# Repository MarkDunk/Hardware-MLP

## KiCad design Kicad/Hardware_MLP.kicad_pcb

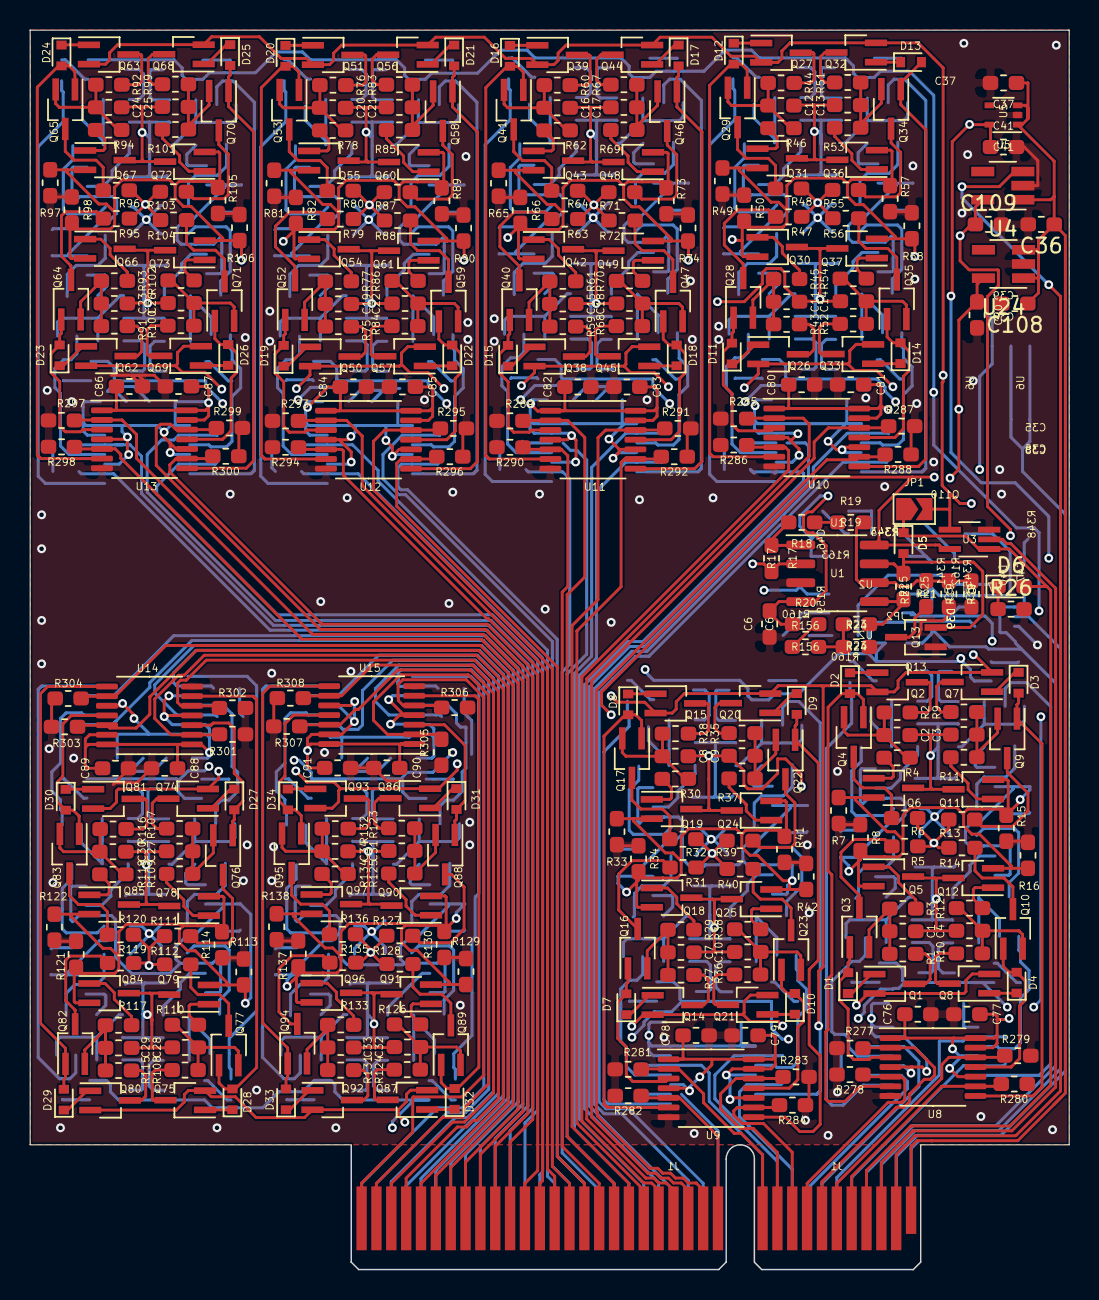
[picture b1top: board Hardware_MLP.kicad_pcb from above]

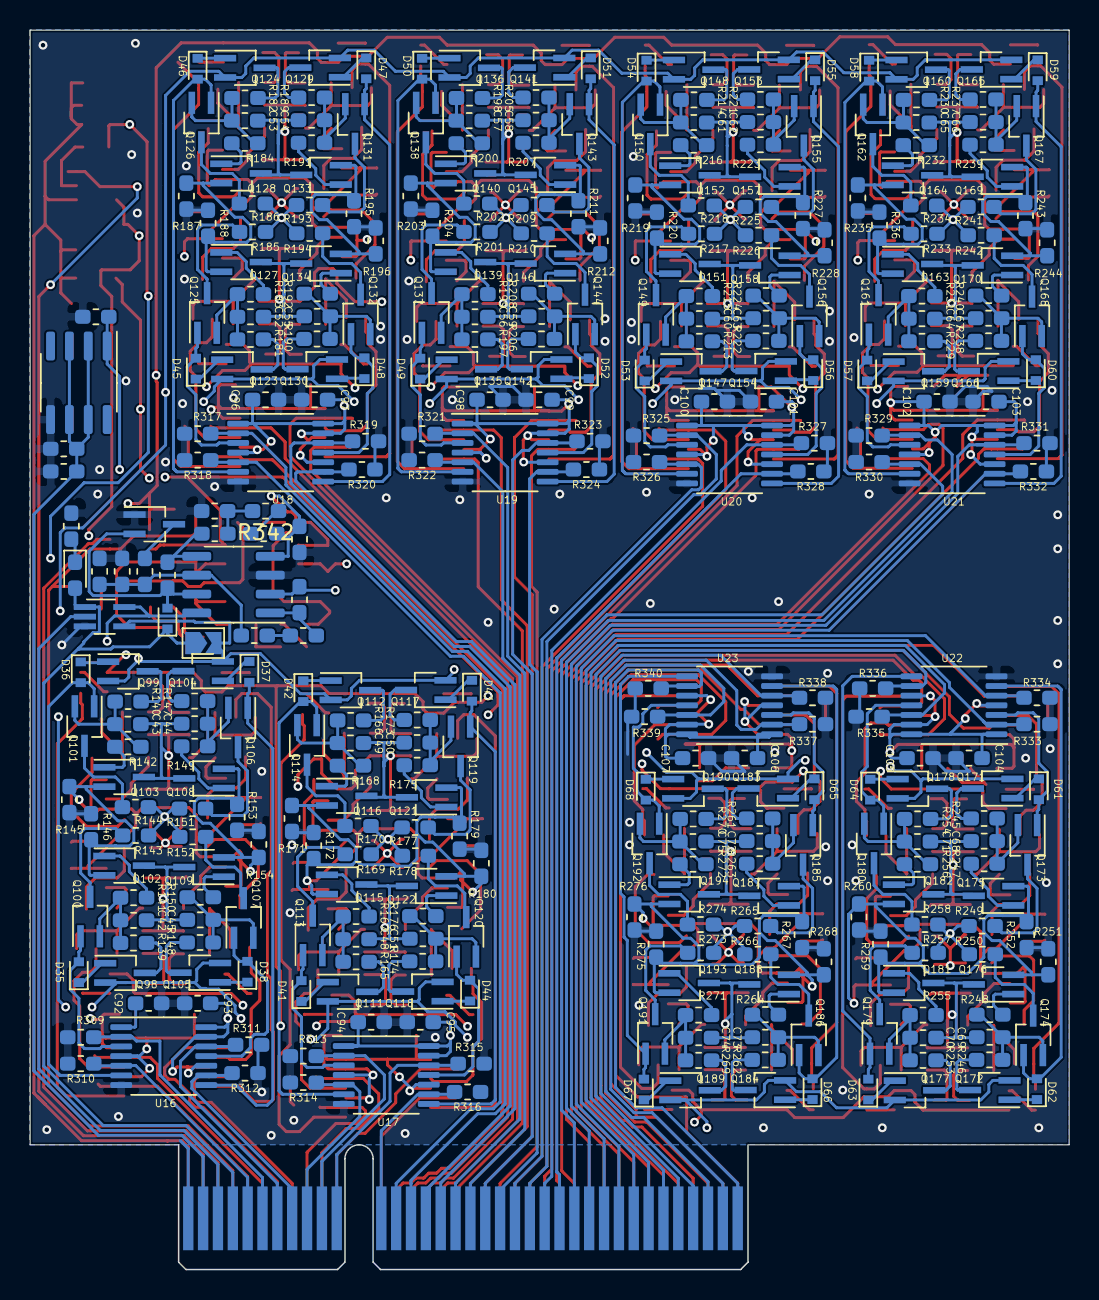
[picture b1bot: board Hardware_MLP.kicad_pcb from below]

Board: 4 copper layers, 70.0 x 83.5 mm, 740 parts (368 on the bottom side), 482 nets.

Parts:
C1, C2, C3, C4, C7, C8, C9, C10, C11, C12, C13, C14, C15, C16, C17, C18, C19, C20, C21, C22, C23, C24, C25, C26, C27, C28, C29, C30, C31, C32, C33, C34, C42, C43, C44, C45, C48, C49, C50, C51, C52, C53, C54, C55, C56, C57, C58, C59, C60, C61, C62, C63, C64, C65, C66, C67, C68, C69, C70, C71, C72, C73, C74, C75: 10uF; C_0603_1608Metric_Pad1.05x0.95mm_HandSolder
C5, C47: 4.7uF; C_0603_1608Metric_Pad1.05x0.95mm_HandSolder
C6, C36, C39, C46, C76, C78, C80, C82, C84, C86, C88, C90, C92, C94, C96, C98, C100, C102, C104, C106, C108: .1uF; C_0603_1608Metric_Pad1.05x0.95mm_HandSolder
C35, C37, C40, C41, C77, C79, C81, C83, C85, C87, C89, C91, C93, C95, C97, C99, C101, C103, C105, C107, C109: 1uF; C_0603_1608Metric_Pad1.05x0.95mm_HandSolder
C38: .33uF; C_0603_1608Metric_Pad1.05x0.95mm_HandSolder
D1, D2, D3, D4, D5, D7, D8, D9, D10, D11, D12, D13, D14, D15, D16, D17, D18, D19, D20, D21, D22, D23, D24, D25, D26, D27, D28, D29, D30, D31, D32, D33, D34, D35, D36, D37, D38, D39, D41, D42, D43, D44, D45, D46, D47, D48, D49, D50, D51, D52, D53, D54, D55, D56, D57, D58, D59, D60, D61, D62, D63, D64, D65, D66, D67, D68: RB521S-30; D_SOD-523
D6, D40: LED; LED_0603_1608Metric_Pad1.05x0.95mm_HandSolder
J1: Neuron_Board_Edge; BUS_PCIexpress_x8
JP1, JP2: SolderJumper_2_Open; SolderJumper-2_P1.3mm_Open_TrianglePad1.0x1.5mm
Q1, Q2, Q3, Q4, Q5, Q6, Q7, Q8, Q9, Q10, Q11, Q12, Q13, Q14, Q15, Q16, Q17, Q18, Q19, Q20, Q21, Q22, Q23, Q24, Q25, Q26, Q27, Q28, Q29, Q30, Q31, Q32, Q33, Q34, Q35, Q36, Q37, Q38, Q39, Q40, Q41, Q42, Q43, Q44, Q45, Q46, Q47, Q48, Q49, Q50, Q51, Q52, Q53, Q54, Q55, Q56, Q57, Q58, Q59, Q60, Q61, Q62, Q63, Q64, Q65, Q66, Q67, Q68, Q69, Q70, Q71, Q72, Q73, Q74, Q75, Q76, Q77, Q78, Q79, Q80, Q81, Q82, Q83, Q84, Q85, Q86, Q87, Q88, Q89, Q90, Q91, Q92, Q93, Q94, Q95, Q96, Q97, Q98, Q99, Q100, Q101, Q102, Q103, Q104, Q105, Q106, Q107, Q108, Q109, Q110, Q111, Q112, Q113, Q114, Q115, Q116, Q117, Q118, Q119, Q120, Q121, Q122, Q123, Q124, Q125, Q126, Q127, Q128, Q129, Q130, Q131, Q132, Q133, Q134, Q135, Q136, Q137, Q138, Q139, Q140, Q141, Q142, Q143, Q144, Q145, Q146, Q147, Q148, Q149, Q150, Q151, Q152, Q153, Q154, Q155, Q156, Q157, Q158, Q159, Q160, Q161, Q162, Q163, Q164, Q165, Q166, Q167, Q168, Q169, Q170, Q171, Q172, Q173, Q174, Q175, Q176, Q177, Q178, Q179, Q180, Q181, Q182, Q183, Q184, Q185, Q186, Q187, Q188, Q189, Q190, Q191, Q192, Q193, Q194: 2SK3018; SOT-323_SC-70_Handsoldering
R1, R2, R3, R4, R7, R8, R9, R10, R11, R12, R15, R16, R27, R28, R29, R30, R33, R34, R35, R36, R37, R38, R41, R42, R43, R44, R45, R46, R49, R50, R51, R52, R53, R54, R57, R58, R59, R60, R61, R62, R65, R66, R67, R68, R69, R70, R73, R74, R75, R76, R77, R78, R81, R82, R83, R84, R85, R86, R89, R90, R91, R92, R93, R94, R97, R98, R99, R100, R101, R102, R105, R106, R107, R108, R109, R110, R113, R114, R115, R116, R117, R118, R121, R122, R123, R124, R125, R126, R129, R130, R131, R132, R133, R134, R137, R138, R139, R140, R141, R142, R145, R146, R147, R148, R149, R150, R153, R154, R165, R166, R167, R168, R171, R172, R173, R174, R175, R176, R179, R180, R181, R182, R183, R184, R187, R188, R189, R190, R191, R192, R195, R196, R197, R198, R199, R200, R203, R204, R205, R206, R207, R208, R211, R212, R213, R214, R215, R216, R219, R220, R221, R222, R223, R224, R227, R228, R229, R230, R231, R232, R235, R236, R237, R238, R239, R240, R243, R244, R245, R246, R247, R248, R251, R252, R253, R254, R255, R256, R259, R260, R261, R262, R263, R264, R267, R268, R269, R270, R271, R272, R275, R276: 100K; R_0603_1608Metric_Pad1.05x0.95mm_HandSolder
R5, R6, R13, R14, R31, R32, R39, R40, R47, R48, R55, R56, R63, R64, R71, R72, R79, R80, R87, R88, R95, R96, R103, R104, R111, R112, R119, R120, R127, R128, R135, R136, R143, R144, R151, R152, R169, R170, R177, R178, R185, R186, R193, R194, R201, R202, R209, R210, R217, R218, R225, R226, R233, R234, R241, R242, R249, R250, R257, R258, R265, R266, R273, R274: 1.5K; R_0603_1608Metric_Pad1.05x0.95mm_HandSolder
R17, R21, R159, R341: 100; R_0603_1608Metric_Pad1.05x0.95mm_HandSolder
R18, R160, R160#2: Rc; R_0603_1608Metric_Pad1.05x0.95mm_HandSolder
R19, R19#2, R23, R24, R25, R156, R162, R343, R344, R345: 10K; R_0603_1608Metric_Pad1.05x0.95mm_HandSolder
R20, R163: 20K; R_0603_1608Metric_Pad1.05x0.95mm_HandSolder
R26, R348: R_LED; R_0603_1608Metric_Pad1.05x0.95mm_HandSolder
R277, R278, R279, R280, R281, R282, R283, R284, R285, R286, R287, R288, R289, R290, R291, R292, R293, R294, R295, R296, R297, R298, R299, R300, R301, R302, R303, R304, R305, R306, R307, R308, R309, R310, R311, R312, R313, R314, R315, R316, R317, R318, R319, R320, R321, R322, R323, R324, R325, R326, R327, R328, R329, R330, R331, R332, R333, R334, R335, R336, R337, R338, R339, R340: 10k; R_0603_1608Metric_Pad1.05x0.95mm_HandSolder
R342: R_0603_1608Metric_Pad1.05x0.95mm_HandSolder
U1, U2: AZ4580; SOIC-8_3.9x4.9mm_P1.27mm
U3, U7: 74AHC1G08; SOT-353_SC-70-5_Handsoldering
U4, U24: TCR2EF; SOT-23-5_HandSoldering
U5: MIC5365-1.2YC5; SOT-353_SC-70-5
U6: MC79L05_SO8; SOIC-8_3.9x4.9mm_P1.27mm
U8, U9, U10, U11, U12, U13, U14, U15, U16, U17, U18, U19, U20, U21, U22, U23: SN74AHCT126; TSSOP-14_4.4x5mm_P0.65mm

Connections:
/5V5: C36.1, C37.1, C108.1, J1.A1, U4.1, U5.1, U5.3, U24.1, U24.3
/-10V: C35.2, C38.2, J1.B2, U6.2, U6.3, U6.6, U6.7
/A Side/Hebb: JP1.2, Q1.2, Q2.2, Q7.2, Q8.2, Q14.2, Q15.2, Q20.2, Q21.2, Q26.2, Q27.2, Q32.2, Q33.2, Q38.2, Q39.2, Q44.2, Q45.2, Q50.2, Q51.2, Q56.2, Q57.2, Q62.2, Q63.2, Q68.2, Q69.2, Q74.2, Q75.2, Q80.2, Q81.2, Q86.2, Q87.2, Q92.2, Q93.2, U3.4
/A Side/WX: R5.1, R6.1, R13.1, R14.1, R17.2, R31.1, R32.1, R39.1, R40.1, R47.1, R48.1, R55.1, R56.1, R63.1, R64.1, R71.1, R72.1, R79.1, R80.1, R87.1, R88.1, R95.1, R96.1, R103.1, R104.1, R111.1, R112.1, R119.1, R120.1, R127.1, R128.1, R135.1, R136.1, U1.2
/A Side/Weight Section 1/X1_CL: D1.2, Q3.1, U8.3
/A Side/Weight Section 1/X2_CL: D2.2, Q4.1, U8.6
/A Side/Weight Section 1/X3_CL: D3.2, Q9.1, U8.8
/A Side/Weight Section 1/X4_CL: D4.2, Q10.1, U8.11
/A Side/sheet60210D35/X1_CL: D19.2, Q52.1, U12.3
/A Side/sheet60210D35/X2_CL: D20.2, Q53.1, U12.6
/A Side/sheet60210D35/X3_CL: D21.2, Q58.1, U12.8
/A Side/sheet60210D35/X4_CL: D22.2, Q59.1, U12.11
/A Side/sheet60210D36/X1_CL: D23.2, Q64.1, U13.3
/A Side/sheet60210D36/X2_CL: D24.2, Q65.1, U13.6
/A Side/sheet60210D36/X3_CL: D25.2, Q70.1, U13.8
/A Side/sheet60210D36/X4_CL: D26.2, Q71.1, U13.11
/A Side/sheet60210D37/X1_CL: D27.2, Q76.1, U14.3
/A Side/sheet60210D37/X2_CL: D28.2, Q77.1, U14.6
/A Side/sheet60210D37/X3_CL: D29.2, Q82.1, U14.8
/A Side/sheet60210D37/X4_CL: D30.2, Q83.1, U14.11
/A Side/sheet60210D38/X1_CL: D31.2, Q88.1, U15.3
/A Side/sheet60210D38/X2_CL: D32.2, Q89.1, U15.6
/A Side/sheet60210D38/X3_CL: D33.2, Q94.1, U15.8
/A Side/sheet60210D38/X4_CL: D34.2, Q95.1, U15.11
/A Side/sheet602109E3/X1_CL: D11.2, Q28.1, U10.3
/A Side/sheet602109E3/X2_CL: D12.2, Q29.1, U10.6
/A Side/sheet602109E3/X3_CL: D13.2, Q34.1, U10.8
/A Side/sheet602109E3/X4_CL: D14.2, Q35.1, U10.11
/A Side/sheet602109E4/X1_CL: D15.2, Q40.1, U11.3
/A Side/sheet602109E4/X2_CL: D16.2, Q41.1, U11.6
/A Side/sheet602109E4/X3_CL: D17.2, Q46.1, U11.8
/A Side/sheet602109E4/X4_CL: D18.2, Q47.1, U11.11
/A Side/sheet6021083A/X1_CL: D7.2, Q16.1, U9.3
/A Side/sheet6021083A/X2_CL: D8.2, Q17.1, U9.6
/A Side/sheet6021083A/X3_CL: D9.2, Q22.1, U9.8
/A Side/sheet6021083A/X4_CL: D10.2, Q23.1, U9.11
/B Side/Hebb: JP2.2, Q98.2, Q99.2, Q104.2, Q105.2, Q111.2, Q112.2, Q117.2, Q118.2, Q123.2, Q124.2, Q129.2, Q130.2, Q135.2, Q136.2, Q141.2, Q142.2, Q147.2, Q148.2, Q153.2, Q154.2, Q159.2, Q160.2, Q165.2, Q166.2, Q171.2, Q172.2, Q177.2, Q178.2, Q183.2, Q184.2, Q189.2, Q190.2, U7.4
/B Side/WX: R143.1, R144.1, R151.1, R152.1, R159.2, R169.1, R170.1, R177.1, R178.1, R185.1, R186.1, R193.1, R194.1, R201.1, R202.1, R209.1, R210.1, R217.1, R218.1, R225.1, R226.1, R233.1, R234.1, R241.1, R242.1, R249.1, R250.1, R257.1, R258.1, R265.1, R266.1, R273.1, R274.1, U2.2
/B Side/Weight Section 1/X1_CL: D35.2, Q100.1, U16.3
/B Side/Weight Section 1/X2_CL: D36.2, Q101.1, U16.6
/B Side/Weight Section 1/X3_CL: D37.2, Q106.1, U16.8
/B Side/Weight Section 1/X4_CL: D38.2, Q107.1, U16.11
/B Side/sheet60210D35/X1_CL: D53.2, Q149.1, U20.3
/B Side/sheet60210D35/X2_CL: D54.2, Q150.1, U20.6
/B Side/sheet60210D35/X3_CL: D55.2, Q155.1, U20.8
/B Side/sheet60210D35/X4_CL: D56.2, Q156.1, U20.11
/B Side/sheet60210D36/X1_CL: D57.2, Q161.1, U21.3
/B Side/sheet60210D36/X2_CL: D58.2, Q162.1, U21.6
/B Side/sheet60210D36/X3_CL: D59.2, Q167.1, U21.8
/B Side/sheet60210D36/X4_CL: D60.2, Q168.1, U21.11
/B Side/sheet60210D37/X1_CL: D61.2, Q173.1, U22.3
/B Side/sheet60210D37/X2_CL: D62.2, Q174.1, U22.6
/B Side/sheet60210D37/X3_CL: D63.2, Q179.1, U22.8
/B Side/sheet60210D37/X4_CL: D64.2, Q180.1, U22.11
/B Side/sheet60210D38/X1_CL: D65.2, Q185.1, U23.3
/B Side/sheet60210D38/X2_CL: D66.2, Q186.1, U23.6
/B Side/sheet60210D38/X3_CL: D67.2, Q191.1, U23.8
/B Side/sheet60210D38/X4_CL: D68.2, Q192.1, U23.11
/B Side/sheet602109E3/X1_CL: D45.2, Q125.1, U18.3
/B Side/sheet602109E3/X2_CL: D46.2, Q126.1, U18.6
/B Side/sheet602109E3/X3_CL: D47.2, Q131.1, U18.8
/B Side/sheet602109E3/X4_CL: D48.2, Q132.1, U18.11
/B Side/sheet602109E4/X1_CL: D49.2, Q137.1, U19.3
/B Side/sheet602109E4/X2_CL: D50.2, Q138.1, U19.6
/B Side/sheet602109E4/X3_CL: D51.2, Q143.1, U19.8
/B Side/sheet602109E4/X4_CL: D52.2, Q144.1, U19.11
/B Side/sheet6021083A/X1_CL: D41.2, Q113.1, U17.3
/B Side/sheet6021083A/X2_CL: D42.2, Q114.1, U17.6
/B Side/sheet6021083A/X3_CL: D43.2, Q119.1, U17.8
/B Side/sheet6021083A/X4_CL: D44.2, Q120.1, U17.11
/F(X)A: D5.1, D6.2, J1.A4, JP1.1, U3.1
/F(X)B: D39.1, D40.2, J1.B4, JP2.1, U7.1
/Train: J1.A2, U4.3
/Vgsbias: C1.2, C2.2, C3.2, C4.2, C7.2, C8.2, C9.2, C10.2, C11.2, C12.2, C13.2, C14.2, C15.2, C16.2, C17.2, C18.2, C19.2, C20.2, C21.2, C22.2, C23.2, C24.2, C25.2, C26.2, C27.2, C28.2, C29.2, C30.2, C31.2, C32.2, C33.2, C34.2, C41.1, C42.2, C43.2, C44.2, C45.2, C48.2, C49.2, C50.2, C51.2, C52.2, C53.2, C54.2, C55.2, C56.2, C57.2, C58.2, C59.2, C60.2, C61.2, C62.2, C63.2, C64.2, C65.2, C66.2, C67.2, C68.2, C69.2, C70.2, C71.2, C72.2, C73.2, C74.2, C75.2, Q5.3, Q6.3, Q11.3, Q12.3, Q18.3, Q19.3, Q24.3, Q25.3, Q30.3, Q31.3, Q36.3, Q37.3, Q42.3, Q43.3, Q48.3, Q49.3, Q54.3, Q55.3, Q60.3, Q61.3, Q66.3, Q67.3, Q72.3, Q73.3, Q78.3, Q79.3, Q84.3, Q85.3, Q90.3, Q91.3, Q96.3, Q97.3, Q102.3, Q103.3, Q108.3, Q109.3, Q115.3, Q116.3, Q121.3, Q122.3, Q127.3, Q128.3, Q133.3, Q134.3, Q139.3, Q140.3, Q145.3, Q146.3, Q151.3, Q152.3, Q157.3, Q158.3, Q163.3, Q164.3, Q169.3, Q170.3, Q175.3, Q176.3, Q181.3, Q182.3, Q187.3, Q188.3, Q193.3, Q194.3, U5.5
/Vs-: C6.2, C39.2, C46.2, R20.1, R163.1, U1.4, U2.4, U6.1
/Vtrain: C109.1, Q5.2, Q6.2, Q11.2, Q12.2, Q18.2, Q19.2, Q24.2, Q25.2, Q30.2, Q31.2, Q36.2, Q37.2, Q42.2, Q43.2, Q48.2, Q49.2, Q54.2, Q55.2, Q60.2, Q61.2, Q66.2, Q67.2, Q72.2, Q73.2, Q78.2, Q79.2, Q84.2, Q85.2, Q90.2, Q91.2, Q96.2, Q97.2, Q102.2, Q103.2, Q108.2, Q109.2, Q115.2, Q116.2, Q121.2, Q122.2, Q127.2, Q128.2, Q133.2, Q134.2, Q139.2, Q140.2, Q145.2, Q146.2, Q151.2, Q152.2, Q157.2, Q158.2, Q163.2, Q164.2, Q169.2, Q170.2, Q175.2, Q176.2, Q181.2, Q182.2, Q187.2, Q188.2, Q193.2, Q194.2, R7.1, R8.1, R15.1, R16.1, R33.1, R34.1, R41.1, R42.1, R49.1, R50.1, R57.1, R58.1, R65.1, R66.1, R73.1, R74.1, R81.1, R82.1, R89.1, R90.1, R97.1, R98.1, R105.1, R106.1, R113.1, R114.1, R121.1, R122.1, R129.1, R130.1, R137.1, R138.1, R145.1, R146.1, R153.1, R154.1, R171.1, R172.1, R179.1, R180.1, R187.1, R188.1, R195.1, R196.1, R203.1, R204.1, R211.1, R212.1, R219.1, R220.1, R227.1, R228.1, R235.1, R236.1, R243.1, R244.1, R251.1, R252.1, R259.1, R260.1, R267.1, R268.1, R275.1, R276.1, U4.5
/X1A: J1.A5, R278.1, U8.5
/X1B: J1.B5, R310.1, U16.5
/X2A: J1.A6, R277.1, U8.2
/X2B: J1.B6, R309.1, U16.2
/X3A: J1.A7, R279.2, U8.12
/X3B: J1.B7, R311.2, U16.12
/X4A: J1.A8, R280.2, U8.9
/X4B: J1.B8, R312.2, U16.9
/X5A: J1.A9, R284.2, U9.9
/X5B: J1.B9, R316.2, U17.9
/X6A: J1.A10, R283.2, U9.12
/X6B: J1.B10, R315.2, U17.12
/X7A: J1.A11, R281.1, U9.2
/X7B: J1.B11, R313.1, U17.2
/X8A: J1.A12, R282.1, U9.5
/X8B: J1.B12, R314.1, U17.5
/X9A: J1.A13, R288.2, U10.9
/X9B: J1.B13, R320.2, U18.9
/X10A: J1.A14, R287.2, U10.12
/X10B: J1.B14, R319.2, U18.12
/X11A: J1.A15, R285.1, U10.2
/X11B: J1.B15, R317.1, U18.2
/X12A: J1.A16, R286.1, U10.5
/X12B: J1.B16, R318.1, U18.5
/X13A: J1.A17, R292.2, U11.9
/X13B: J1.B17, R324.2, U19.9
/X14A: J1.A18, R291.2, U11.12
/X14B: J1.B18, R323.2, U19.12
/X15A: J1.A19, R289.1, U11.2
/X15B: J1.B19, R321.1, U19.2
/X16A: J1.A20, R290.1, U11.5
/X16B: J1.B20, R322.1, U19.5
/X17A: J1.A21, R296.2, U12.9
/X17B: J1.B21, R328.2, U20.9
/X18A: J1.A22, R295.2, U12.12
/X18B: J1.B22, R327.2, U20.12
/X19A: J1.A23, R293.1, U12.2
/X19B: J1.B23, R325.1, U20.2
/X20A: J1.A24, R294.1, U12.5
/X20B: J1.B24, R326.1, U20.5
/X21A: J1.A25, R300.2, U13.9
/X21B: J1.B25, R332.2, U21.9
/X22A: J1.A26, R299.2, U13.12
/X22B: J1.B26, R331.2, U21.12
/X23A: J1.A27, R297.1, U13.2
/X23B: J1.B27, R329.1, U21.2
/X24A: J1.A28, R298.1, U13.5
/X24B: J1.B28, R330.1, U21.5
/X25A: J1.A29, R304.2, U14.9
/X25B: J1.B29, R336.2, U22.9
/X26A: J1.A30, R303.2, U14.12
/X26B: J1.B30, R335.2, U22.12
/X27A: J1.A31, R301.1, U14.2
/X27B: J1.B31, R333.1, U22.2
/X28A: J1.A32, R302.1, U14.5
/X28B: J1.B32, R334.1, U22.5
/X29A: J1.A33, R308.2, U15.9
/X29B: J1.B33, R340.2, U23.9
/X30A: J1.A34, R307.2, U15.12
/X30B: J1.B34, R339.2, U23.12
/X31A: J1.A35, R305.1, U15.2
/X31B: J1.B35, R337.1, U23.2
/X32A: J1.A36, R306.1, U15.5
/X32B: J1.B36, R338.1, U23.5
/YA: J1.A3, U3.2
/YB: J1.B3, U7.2
GND: C5.2, C6.1, C35.1, C36.2, C37.2, C38.1, C39.1, C40.2, C41.2, C46.1, C47.2, C76.2, C77.2, C78.2, C79.2, C80.2, C81.2, C82.2, C83.2, C84.2, C85.2, C86.2, C87.2, C88.2, C89.2, C90.2, C91.2, C92.2, C93.2, C94.2, C95.2, C96.2, C97.2, C98.2, C99.2, C100.2, C101.2, C102.2, C103.2, C104.2, C105.2, C106.2, C107.2, C108.2, C109.2, J1.B1, Q13.1, Q110.1, R7.2, R8.2, R15.2, R16.2, R19#2.1, R24.2, R26.2, R33.2, R34.2, R41.2, R42.2, R49.2, R50.2, R57.2, R58.2, R65.2, R66.2, R73.2, R74.2, R81.2, R82.2, R89.2, R90.2, R97.2, R98.2, R105.2, R106.2, R113.2, R114.2, R121.2, R122.2, R129.2, R130.2, R137.2, R138.2, R145.2, R146.2, R153.2, R154.2, R162.1, R171.2, R172.2, R179.2, R180.2, R187.2, R188.2, R195.2, R196.2, R203.2, R204.2, R211.2, R212.2, R219.2, R220.2, R227.2, R228.2, R235.2, R236.2, R243.2, R244.2, R251.2, R252.2, R259.2, R260.2, R267.2, R268.2, R275.2, R276.2, R277.2, R278.2, R279.1, R280.1, R281.2, R282.2, R283.1, R284.1, R285.2, R286.2, R287.1, R288.1, R289.2, R290.2, R291.1, R292.1, R293.2, R294.2, R295.1, R296.1, R297.2, R298.2, R299.1, R300.1, R301.2, R302.2, R303.1, R304.1, R305.2, R306.2, R307.1, R308.1, R309.2, R310.2, R311.1, R312.1, R313.2, R314.2, R315.1, R316.1, R317.2, R318.2, R319.1, R320.1, R321.2, R322.2, R323.1, R324.1, R325.2, R326.2, R327.1, R328.1, R329.2, R330.2, R331.1, R332.1, R333.2, R334.2, R335.1, R336.1, R337.2, R338.2, R339.1, R340.1, R344.2, R348.2, U1.3, U2.3, U3.3, U4.2, U5.2, U6.5, U7.3, U8.7, U9.7, U10.7, U11.7, U12.7, U13.7, U14.7, U15.7, U16.7, U17.7, U18.7, U19.7, U20.7, U21.7, U22.7, U23.7, U24.2
unnamed: C1.1, Q3.2, R1.1, R3.2
unnamed: C2.1, Q4.2, R2.1, R4.2
unnamed: C3.1, Q9.2, R9.1, R11.2
unnamed: C4.1, Q10.2, R10.1, R12.2
unnamed: C5.1, R19.2, R19#2.2, R21.2, U1.6
unnamed: C7.1, Q16.2, R27.1, R29.2
unnamed: C8.1, Q17.2, R28.1, R30.2
unnamed: C9.1, Q22.2, R35.1, R37.2
unnamed: C10.1, Q23.2, R36.1, R38.2
unnamed: C11.1, Q28.2, R43.1, R45.2
unnamed: C12.1, Q29.2, R44.1, R46.2
unnamed: C13.1, Q34.2, R51.1, R53.2
unnamed: C14.1, Q35.2, R52.1, R54.2
unnamed: C15.1, Q40.2, R59.1, R61.2
unnamed: C16.1, Q41.2, R60.1, R62.2
unnamed: C17.1, Q46.2, R67.1, R69.2
unnamed: C18.1, Q47.2, R68.1, R70.2
unnamed: C19.1, Q52.2, R75.1, R77.2
unnamed: C20.1, Q53.2, R76.1, R78.2
unnamed: C21.1, Q58.2, R83.1, R85.2
unnamed: C22.1, Q59.2, R84.1, R86.2
unnamed: C23.1, Q64.2, R91.1, R93.2
unnamed: C24.1, Q65.2, R92.1, R94.2
unnamed: C25.1, Q70.2, R99.1, R101.2
unnamed: C26.1, Q71.2, R100.1, R102.2
unnamed: C27.1, Q76.2, R107.1, R109.2
unnamed: C28.1, Q77.2, R108.1, R110.2
unnamed: C29.1, Q82.2, R115.1, R117.2
unnamed: C30.1, Q83.2, R116.1, R118.2
unnamed: C31.1, Q88.2, R123.1, R125.2
unnamed: C32.1, Q89.2, R124.1, R126.2
unnamed: C33.1, Q94.2, R131.1, R133.2
unnamed: C34.1, Q95.2, R132.1, R134.2
unnamed: C42.1, Q100.2, R139.1, R141.2
unnamed: C43.1, Q101.2, R140.1, R142.2
unnamed: C44.1, Q106.2, R147.1, R149.2
unnamed: C45.1, Q107.2, R148.1, R150.2
unnamed: C47.1, R160.2, R162.2, R341.2, U2.6
unnamed: C48.1, Q113.2, R165.1, R167.2
unnamed: C49.1, Q114.2, R166.1, R168.2
unnamed: C50.1, Q119.2, R173.1, R175.2
unnamed: C51.1, Q120.2, R174.1, R176.2
unnamed: C52.1, Q125.2, R181.1, R183.2
unnamed: C53.1, Q126.2, R182.1, R184.2
unnamed: C54.1, Q131.2, R189.1, R191.2
unnamed: C55.1, Q132.2, R190.1, R192.2
unnamed: C56.1, Q137.2, R197.1, R199.2
unnamed: C57.1, Q138.2, R198.1, R200.2
unnamed: C58.1, Q143.2, R205.1, R207.2
unnamed: C59.1, Q144.2, R206.1, R208.2
unnamed: C60.1, Q149.2, R213.1, R215.2
unnamed: C61.1, Q150.2, R214.1, R216.2
unnamed: C62.1, Q155.2, R221.1, R223.2
unnamed: C63.1, Q156.2, R222.1, R224.2
unnamed: C64.1, Q161.2, R229.1, R231.2
unnamed: C65.1, Q162.2, R230.1, R232.2
unnamed: C66.1, Q167.2, R237.1, R239.2
unnamed: C67.1, Q168.2, R238.1, R240.2
unnamed: C68.1, Q173.2, R245.1, R247.2
unnamed: C69.1, Q174.2, R246.1, R248.2
unnamed: C70.1, Q179.2, R253.1, R255.2
unnamed: C71.1, Q180.2, R254.1, R256.2
unnamed: C72.1, Q185.2, R261.1, R263.2
unnamed: C73.1, Q186.2, R262.1, R264.2
unnamed: C74.1, Q191.2, R269.1, R271.2
unnamed: C75.1, Q192.2, R270.1, R272.2
unnamed: D1.1, Q1.1
unnamed: D2.1, Q2.1
unnamed: D3.1, Q7.1
unnamed: D4.1, Q8.1
unnamed: D5.2, Q13.2, U1.7
unnamed: D6.1, R26.1
unnamed: D7.1, Q14.1
unnamed: D8.1, Q15.1
unnamed: D9.1, Q20.1
unnamed: D10.1, Q21.1
unnamed: D11.1, Q26.1
unnamed: D12.1, Q27.1
unnamed: D13.1, Q32.1
unnamed: D14.1, Q33.1
unnamed: D15.1, Q38.1
unnamed: D16.1, Q39.1
unnamed: D17.1, Q44.1
unnamed: D18.1, Q45.1
unnamed: D19.1, Q50.1
unnamed: D20.1, Q51.1
unnamed: D21.1, Q56.1
unnamed: D22.1, Q57.1
unnamed: D23.1, Q62.1
unnamed: D24.1, Q63.1
unnamed: D25.1, Q68.1
unnamed: D26.1, Q69.1
unnamed: D27.1, Q74.1
unnamed: D28.1, Q75.1
unnamed: D29.1, Q80.1
unnamed: D30.1, Q81.1
unnamed: D31.1, Q86.1
unnamed: D32.1, Q87.1
unnamed: D33.1, Q92.1
unnamed: D34.1, Q93.1
unnamed: D35.1, Q98.1
unnamed: D36.1, Q99.1
unnamed: D37.1, Q104.1
unnamed: D38.1, Q105.1
unnamed: D39.2, Q110.2, U2.7
unnamed: D40.1, R348.1
unnamed: D41.1, Q111.1
unnamed: D42.1, Q112.1
unnamed: D43.1, Q117.1
unnamed: D44.1, Q118.1
unnamed: D45.1, Q123.1
unnamed: D46.1, Q124.1
unnamed: D47.1, Q129.1
unnamed: D48.1, Q130.1
unnamed: D49.1, Q135.1
unnamed: D50.1, Q136.1
unnamed: D51.1, Q141.1
unnamed: D52.1, Q142.1
unnamed: D53.1, Q147.1
unnamed: D54.1, Q148.1
unnamed: D55.1, Q153.1
unnamed: D56.1, Q154.1
unnamed: D57.1, Q159.1
unnamed: D58.1, Q160.1
unnamed: D59.1, Q165.1
unnamed: D60.1, Q166.1
unnamed: D61.1, Q171.1
unnamed: D62.1, Q172.1
unnamed: D63.1, Q177.1
unnamed: D64.1, Q178.1
unnamed: D65.1, Q183.1
unnamed: D66.1, Q184.1
unnamed: D67.1, Q189.1
unnamed: D68.1, Q190.1
unnamed: Q1.3, R1.2
unnamed: Q2.3, R2.2
unnamed: Q3.3, R5.2
unnamed: Q4.3, R6.2
unnamed: Q5.1, R3.1
unnamed: Q6.1, R4.1
unnamed: Q7.3, R9.2
unnamed: Q8.3, R10.2
unnamed: Q9.3, R13.2
unnamed: Q10.3, R14.2
unnamed: Q11.1, R11.1
unnamed: Q12.1, R12.1
unnamed: Q13.3, R21.1
unnamed: Q14.3, R27.2
unnamed: Q15.3, R28.2
unnamed: Q16.3, R31.2
unnamed: Q17.3, R32.2
unnamed: Q18.1, R29.1
unnamed: Q19.1, R30.1
unnamed: Q20.3, R35.2
unnamed: Q21.3, R36.2
unnamed: Q22.3, R39.2
unnamed: Q23.3, R40.2
unnamed: Q24.1, R37.1
unnamed: Q25.1, R38.1
unnamed: Q26.3, R43.2
unnamed: Q27.3, R44.2
unnamed: Q28.3, R47.2
unnamed: Q29.3, R48.2
unnamed: Q30.1, R45.1
unnamed: Q31.1, R46.1
unnamed: Q32.3, R51.2
unnamed: Q33.3, R52.2
unnamed: Q34.3, R55.2
unnamed: Q35.3, R56.2
unnamed: Q36.1, R53.1
unnamed: Q37.1, R54.1
unnamed: Q38.3, R59.2
unnamed: Q39.3, R60.2
unnamed: Q40.3, R63.2
unnamed: Q41.3, R64.2
unnamed: Q42.1, R61.1
unnamed: Q43.1, R62.1
unnamed: Q44.3, R67.2
unnamed: Q45.3, R68.2
unnamed: Q46.3, R71.2
unnamed: Q47.3, R72.2
unnamed: Q48.1, R69.1
unnamed: Q49.1, R70.1
unnamed: Q50.3, R75.2
unnamed: Q51.3, R76.2
unnamed: Q52.3, R79.2
unnamed: Q53.3, R80.2
unnamed: Q54.1, R77.1
unnamed: Q55.1, R78.1
unnamed: Q56.3, R83.2
unnamed: Q57.3, R84.2
unnamed: Q58.3, R87.2
unnamed: Q59.3, R88.2
unnamed: Q60.1, R85.1
unnamed: Q61.1, R86.1
unnamed: Q62.3, R91.2
unnamed: Q63.3, R92.2
unnamed: Q64.3, R95.2
unnamed: Q65.3, R96.2
unnamed: Q66.1, R93.1
unnamed: Q67.1, R94.1
unnamed: Q68.3, R99.2
unnamed: Q69.3, R100.2
unnamed: Q70.3, R103.2
unnamed: Q71.3, R104.2
unnamed: Q72.1, R101.1
unnamed: Q73.1, R102.1
unnamed: Q74.3, R107.2
unnamed: Q75.3, R108.2
unnamed: Q76.3, R111.2
unnamed: Q77.3, R112.2
unnamed: Q78.1, R109.1
unnamed: Q79.1, R110.1
unnamed: Q80.3, R115.2
unnamed: Q81.3, R116.2
unnamed: Q82.3, R119.2
unnamed: Q83.3, R120.2
unnamed: Q84.1, R117.1
unnamed: Q85.1, R118.1
unnamed: Q86.3, R123.2
unnamed: Q87.3, R124.2
unnamed: Q88.3, R127.2
unnamed: Q89.3, R128.2
unnamed: Q90.1, R125.1
unnamed: Q91.1, R126.1
unnamed: Q92.3, R131.2
unnamed: Q93.3, R132.2
unnamed: Q94.3, R135.2
unnamed: Q95.3, R136.2
unnamed: Q96.1, R133.1
unnamed: Q97.1, R134.1
unnamed: Q98.3, R139.2
unnamed: Q99.3, R140.2
unnamed: Q100.3, R143.2
unnamed: Q101.3, R144.2
unnamed: Q102.1, R141.1
unnamed: Q103.1, R142.1
unnamed: Q104.3, R147.2
unnamed: Q105.3, R148.2
unnamed: Q106.3, R151.2
unnamed: Q107.3, R152.2
unnamed: Q108.1, R149.1
unnamed: Q109.1, R150.1
unnamed: Q110.3, R341.1
unnamed: Q111.3, R165.2
unnamed: Q112.3, R166.2
unnamed: Q113.3, R169.2
unnamed: Q114.3, R170.2
unnamed: Q115.1, R167.1
unnamed: Q116.1, R168.1
unnamed: Q117.3, R173.2
unnamed: Q118.3, R174.2
unnamed: Q119.3, R177.2
unnamed: Q120.3, R178.2
unnamed: Q121.1, R175.1
unnamed: Q122.1, R176.1
unnamed: Q123.3, R181.2
unnamed: Q124.3, R182.2
unnamed: Q125.3, R185.2
unnamed: Q126.3, R186.2
unnamed: Q127.1, R183.1
unnamed: Q128.1, R184.1
unnamed: Q129.3, R189.2
unnamed: Q130.3, R190.2
unnamed: Q131.3, R193.2
unnamed: Q132.3, R194.2
unnamed: Q133.1, R191.1
unnamed: Q134.1, R192.1
unnamed: Q135.3, R197.2
unnamed: Q136.3, R198.2
unnamed: Q137.3, R201.2
unnamed: Q138.3, R202.2
unnamed: Q139.1, R199.1
unnamed: Q140.1, R200.1
unnamed: Q141.3, R205.2
unnamed: Q142.3, R206.2
unnamed: Q143.3, R209.2
unnamed: Q144.3, R210.2
unnamed: Q145.1, R207.1
unnamed: Q146.1, R208.1
unnamed: Q147.3, R213.2
unnamed: Q148.3, R214.2
unnamed: Q149.3, R217.2
unnamed: Q150.3, R218.2
unnamed: Q151.1, R215.1
unnamed: Q152.1, R216.1
unnamed: Q153.3, R221.2
unnamed: Q154.3, R222.2
unnamed: Q155.3, R225.2
unnamed: Q156.3, R226.2
unnamed: Q157.1, R223.1
unnamed: Q158.1, R224.1
unnamed: Q159.3, R229.2
unnamed: Q160.3, R230.2
unnamed: Q161.3, R233.2
unnamed: Q162.3, R234.2
unnamed: Q163.1, R231.1
unnamed: Q164.1, R232.1
unnamed: Q165.3, R237.2
unnamed: Q166.3, R238.2
unnamed: Q167.3, R241.2
unnamed: Q168.3, R242.2
unnamed: Q169.1, R239.1
unnamed: Q170.1, R240.1
unnamed: Q171.3, R245.2
unnamed: Q172.3, R246.2
unnamed: Q173.3, R249.2
unnamed: Q174.3, R250.2
unnamed: Q175.1, R247.1
unnamed: Q176.1, R248.1
unnamed: Q177.3, R253.2
unnamed: Q178.3, R254.2
unnamed: Q179.3, R257.2
unnamed: Q180.3, R258.2
unnamed: Q181.1, R255.1
unnamed: Q182.1, R256.1
unnamed: Q183.3, R261.2
unnamed: Q184.3, R262.2
unnamed: Q185.3, R265.2
unnamed: Q186.3, R266.2
unnamed: Q187.1, R263.1
unnamed: Q188.1, R264.1
unnamed: Q189.3, R269.2
unnamed: Q190.3, R270.2
unnamed: Q191.3, R273.2
unnamed: Q192.3, R274.2
unnamed: Q193.1, R271.1
unnamed: Q194.1, R272.1
unnamed: R17.1, R18.2, U1.1
unnamed: R18.1, R19.1
unnamed: R23.1, R25.2, U1.5
unnamed: R23.2, R24.1
unnamed: R159.1, R160#2.2, U2.1
unnamed: R160.1, R160#2.1
unnamed: R163.2, R342.1
unnamed: R342.2, R343.2, R344.1
unnamed: R343.1, R345.2, U2.5
VCC: U3.5, U7.5
Vs+: C40.1, C76.1, C77.1, C78.1, C79.1, C80.1, C81.1, C82.1, C83.1, C84.1, C85.1, C86.1, C87.1, C88.1, C89.1, C90.1, C91.1, C92.1, C93.1, C94.1, C95.1, C96.1, C97.1, C98.1, C99.1, C100.1, C101.1, C102.1, C103.1, C104.1, C105.1, C106.1, C107.1, U1.8, U2.8, U8.1, U8.4, U8.10, U8.13, U8.14, U9.1, U9.4, U9.10, U9.13, U9.14, U10.1, U10.4, U10.10, U10.13, U10.14, U11.1, U11.4, U11.10, U11.13, U11.14, U12.1, U12.4, U12.10, U12.13, U12.14, U13.1, U13.4, U13.10, U13.13, U13.14, U14.1, U14.4, U14.10, U14.13, U14.14, U15.1, U15.4, U15.10, U15.13, U15.14, U16.1, U16.4, U16.10, U16.13, U16.14, U17.1, U17.4, U17.10, U17.13, U17.14, U18.1, U18.4, U18.10, U18.13, U18.14, U19.1, U19.4, U19.10, U19.13, U19.14, U20.1, U20.4, U20.10, U20.13, U20.14, U21.1, U21.4, U21.10, U21.13, U21.14, U22.1, U22.4, U22.10, U22.13, U22.14, U23.1, U23.4, U23.10, U23.13, U23.14, U24.5

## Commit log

2021-02-04 Initial Board Layout
    Initial hardware selection and layout.
2021-02-08 Likely Final Component Values
    Most values for components that are not dependent on synapse number have been selected.
2021-02-08 Added gitignore
